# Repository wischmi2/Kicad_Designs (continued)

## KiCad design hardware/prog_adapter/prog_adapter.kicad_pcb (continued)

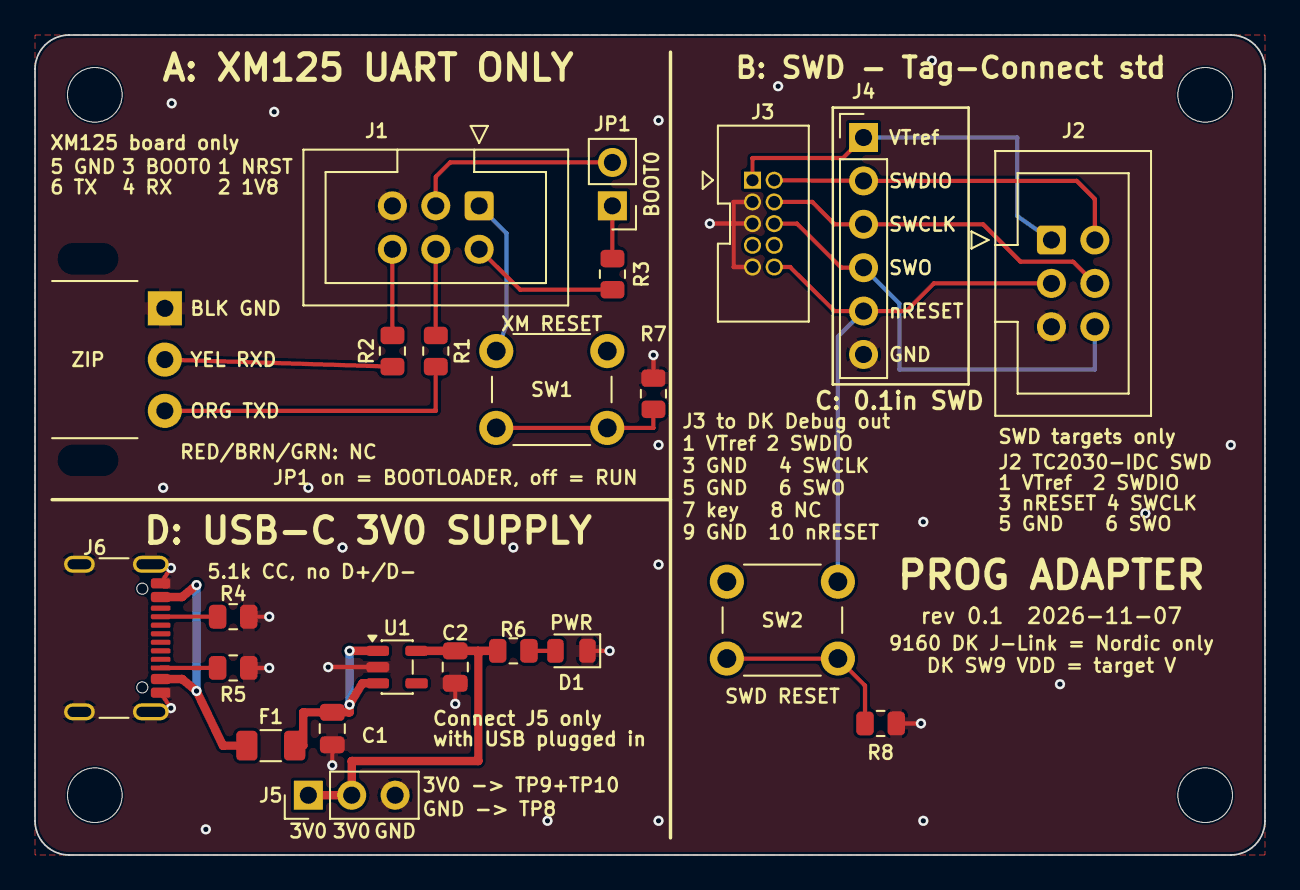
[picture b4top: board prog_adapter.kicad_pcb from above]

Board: 2 copper layers, 72.0 x 48.0 mm, 27 parts (0 on the bottom side), 22 nets.

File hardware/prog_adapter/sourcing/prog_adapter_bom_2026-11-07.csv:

Ref,Qty,Value,MPN,Manufacturer,DigiKey,Mouser,Unit price USD (qty 1),Stock 2026-11-07,Note
"J1,J2",2,2x3 box header,SSK05-BH-254-B3,Same Sky,2223-SSK05-BH-254-B3-ND,179-SSK05BH254B3,0.24,DK 1234 / Mouser 1977,shrouded keyed 2.54 mm THT
J3,1,2x5 1.27 mm box header,3220-10-0100-00,CNC Tech,1175-1627-ND,-,0.59,DK 648962,shrouded keyed THT; not found at Mouser
J4,1,1x6 2.54 mm header,PEC06SAAN,Sullins Connector Solutions,35-PEC06SAAN-ND,-,0.41,DK 24626,
J5,1,1x3 2.54 mm header,PEC03SAAN,Sullins Connector Solutions,35-PEC03SAAN-ND,-,0.22,DK 55156,
JP1,1,1x2 2.54 mm header,PEC02SAAN,Sullins Connector Solutions,35-PEC02SAAN-ND,-,0.16,DK 112334,
JP1 shunt,1,shunt 2.54 mm,SPC02SYAN,Sullins Connector Solutions,S9001-ND,-,0.10,DK 1441283,no footprint
J6,1,USB-C receptacle,USB4105-GF-A,GCT,2073-USB4105-GF-ACT-ND,640-USB4105-GF-A,0.80,DK 138469 / Mouser 390294,power only
"R1,R2",2,330R 0805,RC0805FR-07330RL,YAGEO,311-330CRCT-ND,603-RC0805FR-07330RL,0.10,DK 328688 / Mouser 337103,
"R3,R6",2,1k 0805,RC0805FR-071KL,YAGEO,311-1.00KCRCT-ND,603-RC0805FR-071KL,0.10,DK 407380 / Mouser 2104909,
"R4,R5",2,5.1k 0805,RC0805FR-075K1L,YAGEO,311-5.10KCRCT-ND,603-RC0805FR-075K1L,0.10,DK 1090000 / Mouser 126577,
"R7,R8",2,100R 0805,RC0805FR-07100RL,YAGEO,311-100CRCT-ND,603-RC0805FR-07100RL,0.10,DK 4667 / Mouser 221408,series with SW1/SW2 (review S1); live check 2026-11-07
"C1,C2",2,10u 25V X5R 0805,CC0805KKX5R8BB106,YAGEO,311-1869-1-ND,603-CC805KKX5R8BB106,0.44,DK 0 / Mouser 40574,buy at Mouser
D1,1,green LED 0805,LTST-C171GKT,Lite-On,160-1423-1-ND,859-LTST-C171GKT,0.15,DK 101891 / Mouser 207598,
F1,1,PTC 0.5 A 1206,MF-NSMF050-2,Bourns,MF-NSMF050-2CT-ND,652-MF-NSMF050-2,0.40,DK 60712 / Mouser 16856,
U1,1,LDO 3.0 V 500 mA SOT-23-5,TLV75530PDBVR,Texas Instruments,296-TLV75530PDBVRCT-ND,595-TLV75530PDBVR,0.32,DK 3168 / Mouser 16873,
"SW1,SW2",2,tact 6x6 THT,B3F-1000,Omron (Aratas),SW400-ND,653-B3F-1000,0.35,DK 20482 / Mouser 24727,
J7,0,FTDI wire pads,-,-,-,-,0,-,copper only (not a part)
"H1-H4",0,M3 holes,-,-,-,-,0,-,NPTH
CABLE,1,TC2030-IDC cable (legged),TC2030-IDC,Tag-Connect,TC2030-IDC-ND,-,44.58,DK 245,off-board; one cable serves J1 and J2
CABLE,1,1.8 V USB-UART,TTL-232RG-VREG1V8-WE,FTDI,768-1070-ND,895-TTL232RGVREG1V8W,27.34,DK 6 / Mouser 808,off-board; wires solder to J7
CABLE,1,10-pin 1.27 mm ribbon 6 in,FFSD-05-D-06.00-01-N,Samtec,SAM8218-ND,200-FFSD05D06.0001N,11.39,DK 1591 / Mouser 13408,off-board; DK Debug out to J3 (only if you don't have one)

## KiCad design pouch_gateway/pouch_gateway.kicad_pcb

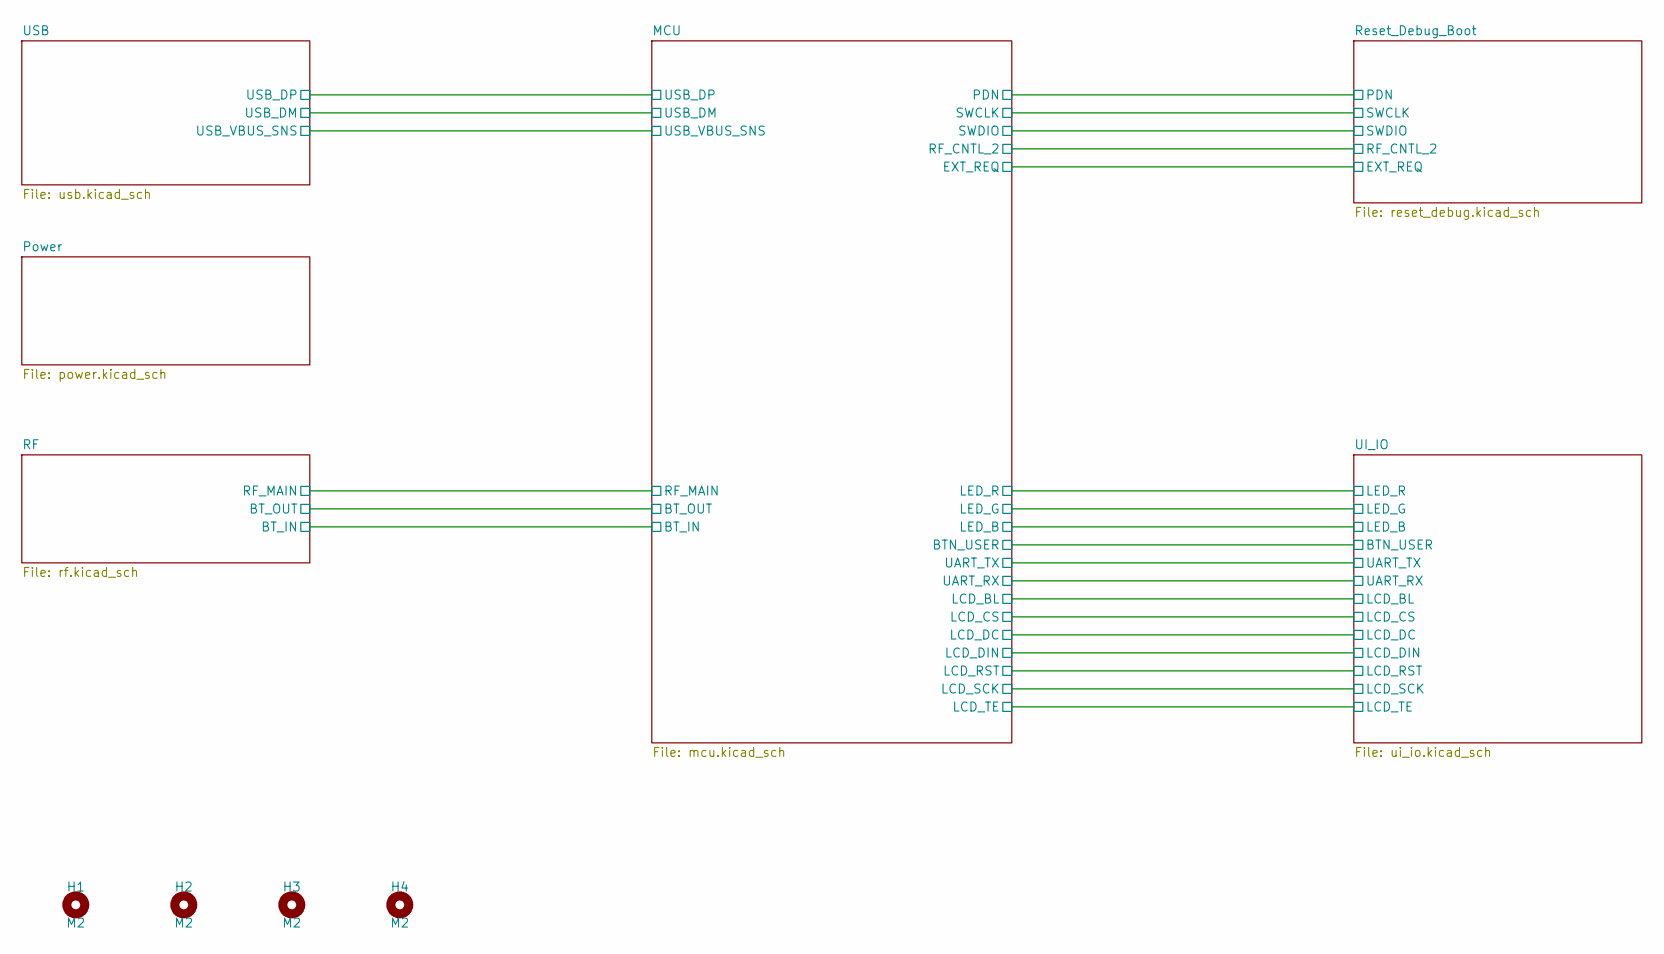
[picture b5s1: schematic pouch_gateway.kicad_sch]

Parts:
H1, H2, H3, H4: M2; MountingHole_2.2mm_M2

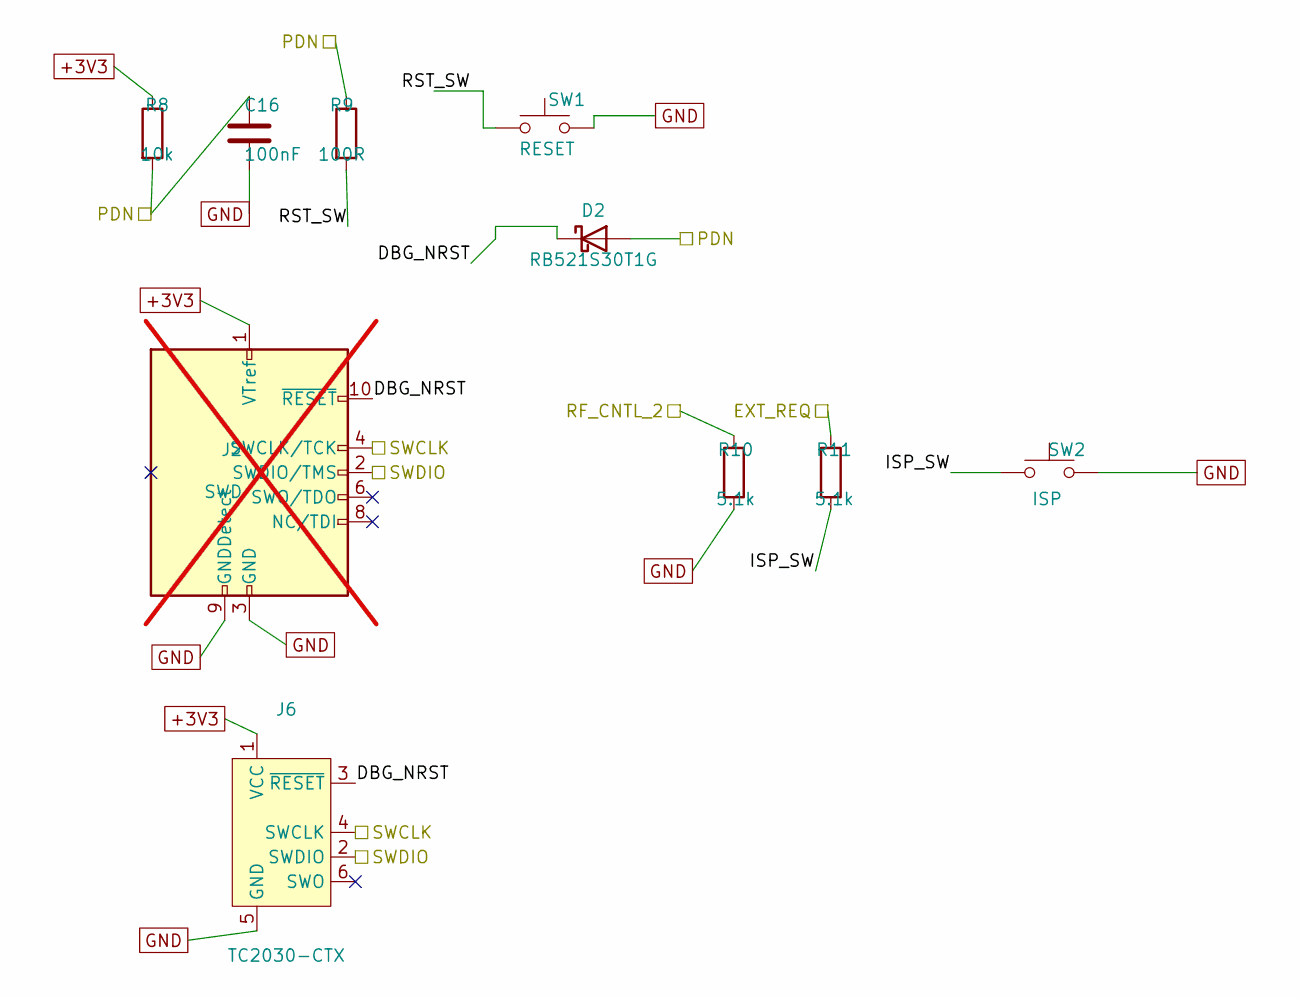
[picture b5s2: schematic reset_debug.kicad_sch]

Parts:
C16: 100nF; C_0402_1005Metric; LCSC C1525
D2: RB521S30T1G; D_SOD-523; LCSC C145179
J2: SWD; PinHeader_2x05_P1.27mm_Vertical_SMD; MPN FTSH-105-01-L-DV-K-TR; LCSC C448647; not fitted
J6: TC2030-CTX; Tag-Connect_TC2030-IDC-FP_2x03_P1.27mm_Vertical
R8: 10k; R_0402_1005Metric; LCSC C25744
R9: 100R; R_0402_1005Metric; LCSC C25076
R10, R11: 5.1k; R_0402_1005Metric; LCSC C25905
SW1: RESET; SW_Push_1P1T_NO_CK_KMR2; LCSC C72443
SW2: ISP; SW_Push_1P1T_NO_CK_KMR2; LCSC C72443

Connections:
+3V3: J2.1 (VTref), J6.1 (VCC), R8.1; also elsewhere on the board
/MCU/EXT_REQ: R11.1; also elsewhere on the board
/MCU/PDN: C16.1, D2.2 (A), R8.2, R9.1; also elsewhere on the board
/MCU/RF_CNTL_2: R10.1; also elsewhere on the board
/MCU/SWCLK: J2.4 (SWCLK/TCK), J6.4 (SWCLK); also elsewhere on the board
/MCU/SWDIO: J2.2 (SWDIO/TMS), J6.2 (SWDIO); also elsewhere on the board
/Reset_Debug_Boot/DBG_NRST: D2.1 (K), J2.10 (~RESET), J6.3 (~RESET)
/Reset_Debug_Boot/ISP_SW: R11.2, SW2.1
/Reset_Debug_Boot/RST_SW: R9.2, SW1.1
GND: C16.2, J2.3 (GND), J2.5 (GND), J2.9 (GNDDetect), J6.5 (GND), R10.2, SW1.2, SW2.2; also elsewhere on the board

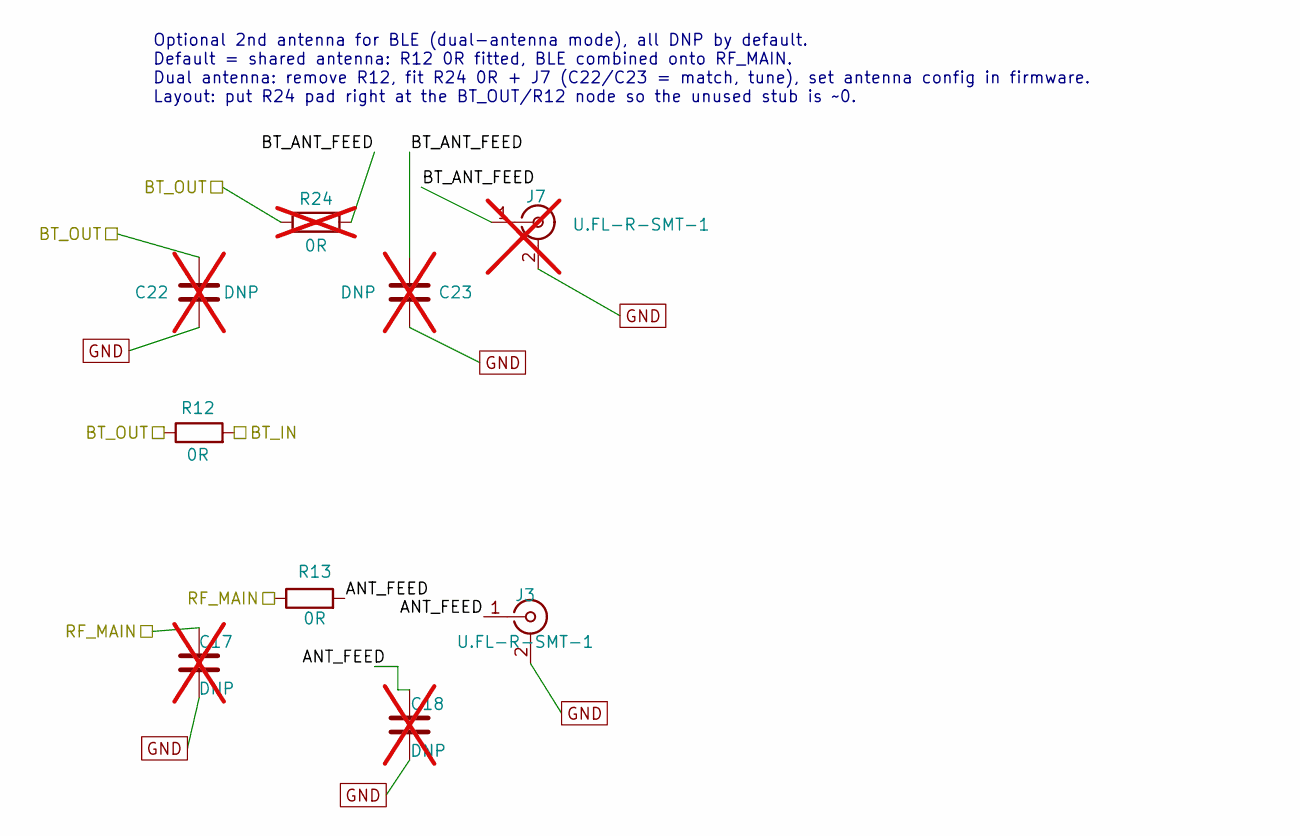
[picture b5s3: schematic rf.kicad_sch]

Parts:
C17, C18: DNP; C_0402_1005Metric; not fitted
C22, C23: DNP; C_0402_1005Metric; LCSC C1525; not fitted
J3: U.FL-R-SMT-1; U.FL_Hirose_U.FL-R-SMT-1_Vertical; LCSC C128668
J7: U.FL-R-SMT-1; U.FL_Hirose_U.FL-R-SMT-1_Vertical; LCSC C128668; not fitted
R12, R13: 0R; R_0402_1005Metric; LCSC C17168
R24: 0R; R_0402_1005Metric; LCSC C17168; not fitted

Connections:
/MCU/BT_IN: R12.2; also elsewhere on the board
/MCU/BT_OUT: C22.1, R12.1, R24.1; also elsewhere on the board
/MCU/RF_MAIN: C17.1, R13.1; also elsewhere on the board
/RF/ANT_FEED: C18.1, J3.1 (In), R13.2
/RF/BT_ANT_FEED: C23.1, J7.1 (In), R24.2
GND: C17.2, C18.2, C22.2, C23.2, J3.2 (Ext), J7.2 (Ext); also elsewhere on the board

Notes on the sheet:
Optional 2nd antenna for BLE (dual-antenna mode), all DNP by default. Default = shared antenna: R12 0R fitted, BLE combined onto RF_MAIN. Dual antenna: remove R12, fit R24 0R + J7 (C22/C23 = match, tune), set antenna config in firmware. Layout: put R24 pad right at the BT_OUT/R12 node so the unused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

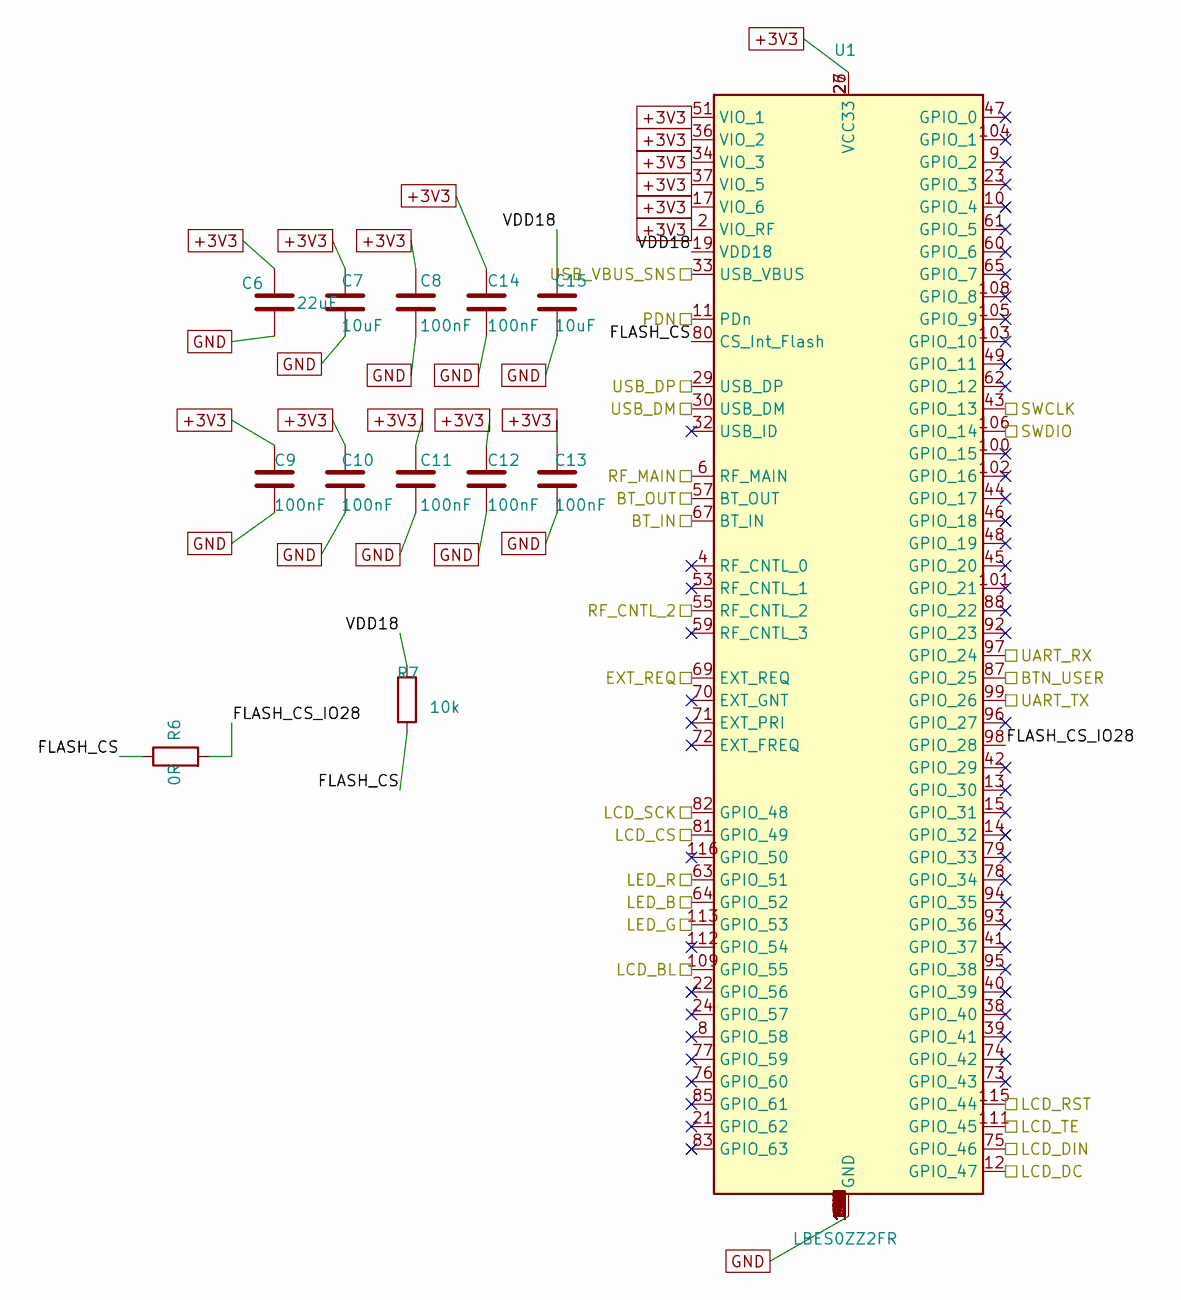
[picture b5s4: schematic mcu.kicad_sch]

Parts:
C6: 22uF; C_0805_2012Metric; LCSC C45783
C7, C15: 10uF; C_0603_1608Metric; LCSC C19702
C8, C9, C10, C11, C12, C13, C14: 100nF; C_0402_1005Metric; LCSC C1525
R6: 0R; R_0402_1005Metric; LCSC C17168
R7: 10k; R_0402_1005Metric; LCSC C25744
U1: LBES0ZZ2FR; Murata_LBES0ZZ2FR; MPN LBES0ZZ2FR-580

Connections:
+3V3: C6.1, C7.1, C8.1, C9.1, C10.1, C11.1, C12.1, C13.1, C14.1, U1.2 (VIO_RF), U1.17 (VIO_6), U1.26 (VCC33), U1.27 (VCC33), U1.34 (VIO_3), U1.36 (VIO_2), U1.37 (VIO_5), U1.51 (VIO_1); also elsewhere on the board
/MCU/BTN_USER: U1.87 (GPIO_25); also elsewhere on the board
/MCU/BT_IN: U1.67 (BT_IN); also elsewhere on the board
/MCU/BT_OUT: U1.57 (BT_OUT); also elsewhere on the board
/MCU/EXT_REQ: U1.69 (EXT_REQ); also elsewhere on the board
/MCU/FLASH_CS: R6.1, R7.2, U1.80 (CS_Int_Flash)
/MCU/FLASH_CS_IO28: R6.2, U1.98 (GPIO_28)
/MCU/LCD_BL: U1.109 (GPIO_55); also elsewhere on the board
/MCU/LCD_CS: U1.81 (GPIO_49); also elsewhere on the board
/MCU/LCD_DC: U1.12 (GPIO_47); also elsewhere on the board
/MCU/LCD_DIN: U1.75 (GPIO_46); also elsewhere on the board
/MCU/LCD_RST: U1.115 (GPIO_44); also elsewhere on the board
/MCU/LCD_SCK: U1.82 (GPIO_48); also elsewhere on the board
/MCU/LCD_TE: U1.111 (GPIO_45); also elsewhere on the board
/MCU/LED_B: U1.64 (GPIO_52); also elsewhere on the board
/MCU/LED_G: U1.113 (GPIO_53); also elsewhere on the board
/MCU/LED_R: U1.63 (GPIO_51); also elsewhere on the board
/MCU/PDN: U1.11 (PDn); also elsewhere on the board
/MCU/RF_CNTL_2: U1.55 (RF_CNTL_2); also elsewhere on the board
/MCU/RF_MAIN: U1.6 (RF_MAIN); also elsewhere on the board
/MCU/SWCLK: U1.43 (GPIO_13); also elsewhere on the board
/MCU/SWDIO: U1.106 (GPIO_14); also elsewhere on the board
/MCU/UART_RX: U1.97 (GPIO_24); also elsewhere on the board
/MCU/UART_TX: U1.99 (GPIO_26); also elsewhere on the board
/MCU/USB_DM: U1.30 (USB_DM); also elsewhere on the board
/MCU/USB_DP: U1.29 (USB_DP); also elsewhere on the board
/MCU/USB_VBUS_SNS: U1.33 (USB_VBUS); also elsewhere on the board
/MCU/VDD18: C15.1, R7.1, U1.19 (VDD18)
GND: C6.2, C7.2, C8.2, C9.2, C10.2, C11.2, C12.2, C13.2, C14.2, C15.2, U1.1 (GND), U1.3 (GND), U1.5 (GND), U1.7 (GND), U1.16 (GND), U1.18 (GND), U1.20 (GND), U1.25 (GND), U1.28 (GND), U1.31 (GND), U1.35 (GND), U1.50 (GND), U1.52 (GND), U1.54 (GND), U1.56 (GND), U1.58 (GND), U1.66 (GND), U1.68 (GND), U1.84 (GND), U1.86 (GND), U1.89 (GND), U1.90 (GND), U1.91 (GND), U1.107 (GND), U1.110 (GND), U1.114 (GND), U1.117 (GND), U1.118 (GND), U1.119 (GND), U1.120 (GND), U1.121 (GND), U1.122 (GND), U1.123 (GND), U1.124 (GND), U1.125 (GND), U1.126 (GND), U1.127 (GND), U1.128 (GND), U1.129 (GND), U1.130 (GND), U1.131 (GND), U1.132 (GND), U1.133 (GND), U1.134 (GND), U1.135 (GND), U1.136 (GND), U1.137 (GND), U1.138 (GND), U1.139 (GND), U1.140 (GND); also elsewhere on the board

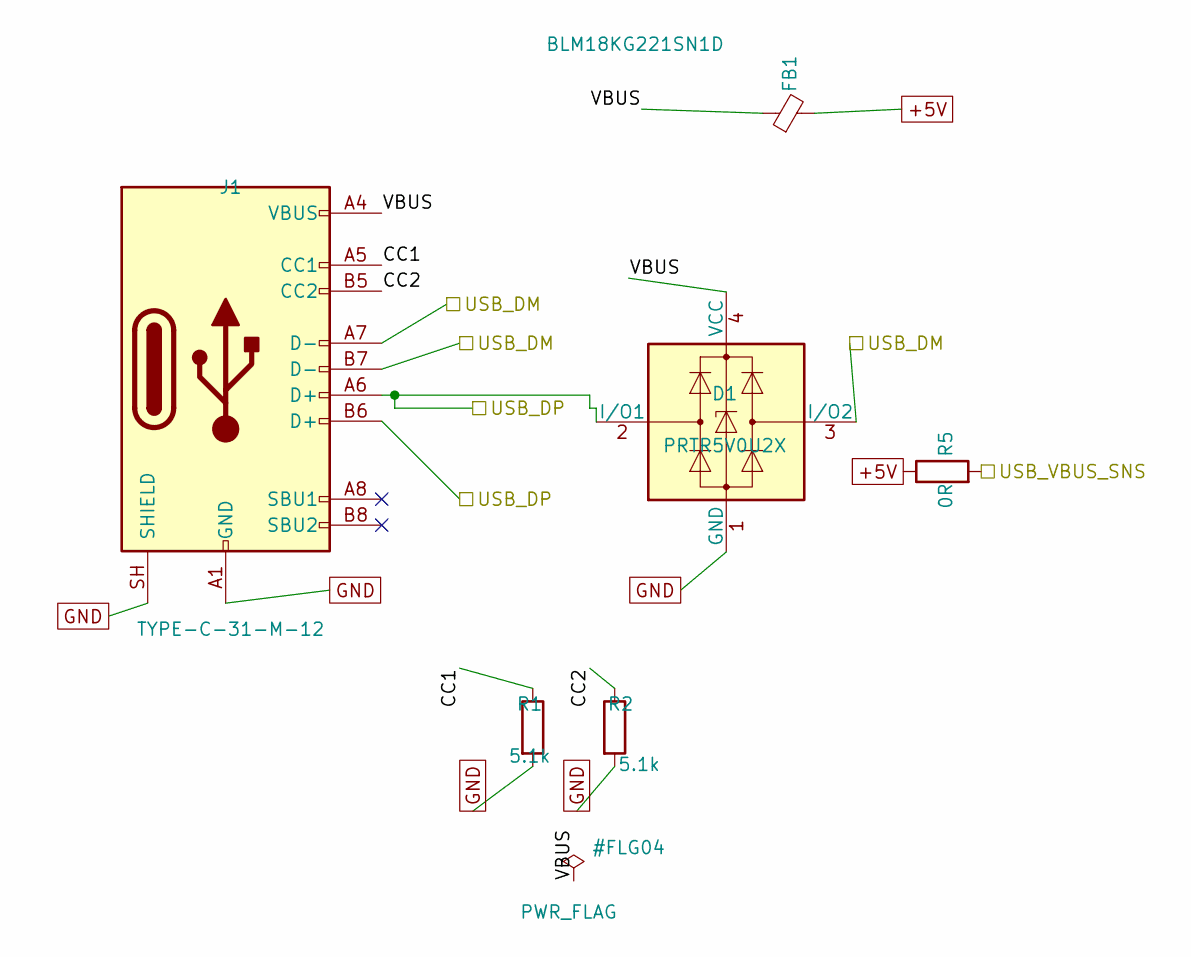
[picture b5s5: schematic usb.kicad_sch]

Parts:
D1: PRTR5V0U2X; SOT-143; LCSC C21713980
FB1: BLM18KG221SN1D; L_0603_1608Metric; LCSC C88980
J1: TYPE-C-31-M-12; USB_C_Receptacle_HRO_TYPE-C-31-M-12; LCSC C165948
R1, R2: 5.1k; R_0402_1005Metric; LCSC C25905
R5: 0R; R_0402_1005Metric; LCSC C17168

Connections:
+5V: FB1.2, R5.1; also elsewhere on the board
/MCU/USB_DM: D1.3 (I/O2), J1.A7 (D-), J1.B7 (D-); also elsewhere on the board
/MCU/USB_DP: D1.2 (I/O1), J1.A6 (D+), J1.B6 (D+); also elsewhere on the board
/MCU/USB_VBUS_SNS: R5.2; also elsewhere on the board
/USB/CC1: J1.A5 (CC1), R1.1
/USB/CC2: J1.B5 (CC2), R2.1
/USB/VBUS: D1.4 (VCC), FB1.1, J1.A4 (VBUS), J1.A9 (VBUS), J1.B4 (VBUS), J1.B9 (VBUS)
GND: D1.1 (GND), J1.A1 (GND), J1.A12 (GND), J1.B1 (GND), J1.B12 (GND), J1.SH (SHIELD), R1.2, R2.2; also elsewhere on the board

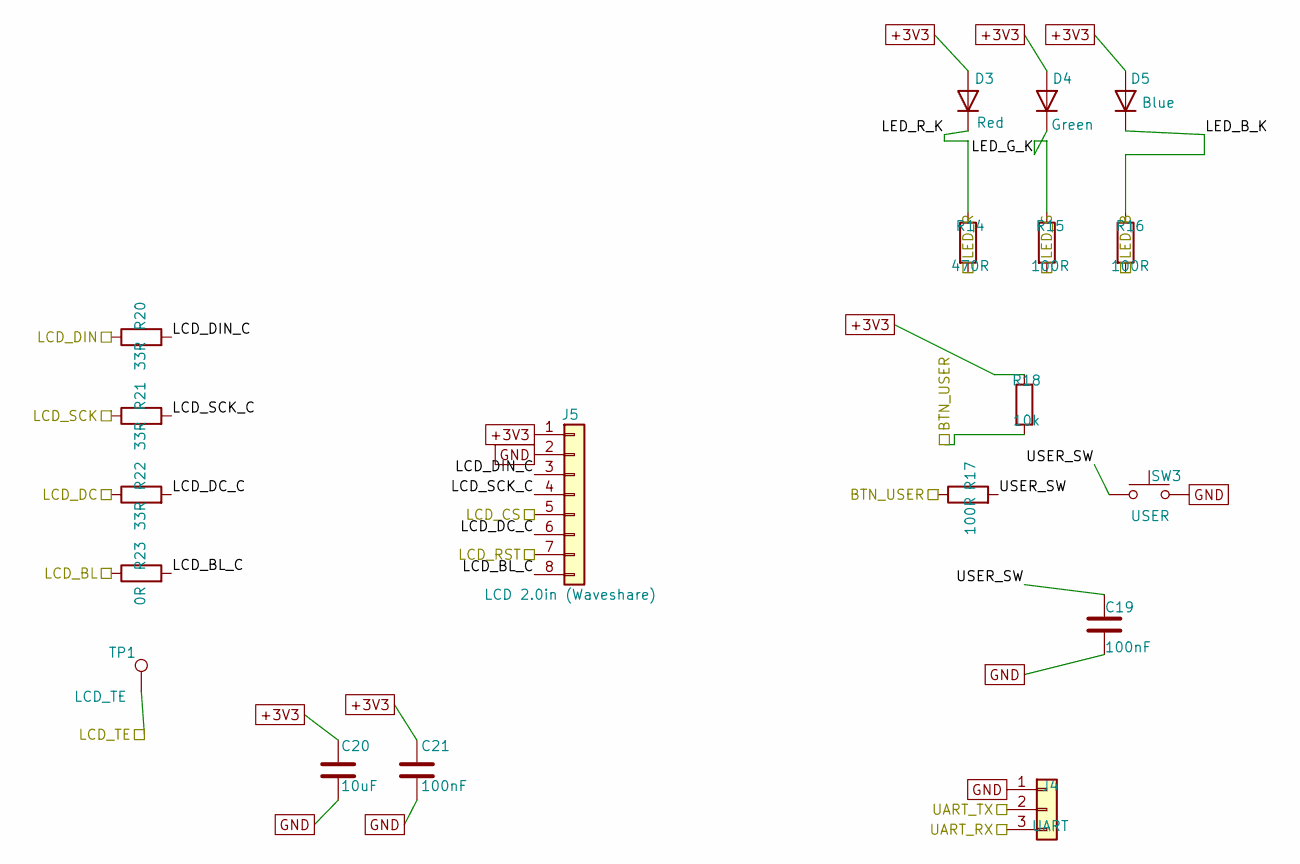
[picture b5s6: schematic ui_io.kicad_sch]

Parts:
C19, C21: 100nF; C_0402_1005Metric; LCSC C1525
C20: 10uF; C_0603_1608Metric; LCSC C19702
D3: Red; LED_0603_1608Metric; LCSC C2286
D4: Green; LED_0805_2012Metric; LCSC C2297
D5: Blue; LED_0603_1608Metric; LCSC C125096
J4: UART; PinHeader_1x03_P2.54mm_Vertical; MPN PZ254V-11-03P; LCSC C2937625
J5: LCD 2.0in (Waveshare); JST_PH_S8B-PH-K_1x08_P2.00mm_Horizontal; MPN S8B-PH-K-S(LF)(SN); LCSC C157915
R14: 470R; R_0402_1005Metric; LCSC C25117
R15, R16, R17: 100R; R_0402_1005Metric; LCSC C25076
R18: 10k; R_0402_1005Metric; LCSC C25744
R20, R21, R22: 33R; R_0402_1005Metric; LCSC C25105
R23: 0R; R_0402_1005Metric; LCSC C17168
SW3: USER; SW_Push_1P1T_NO_CK_KMR2; LCSC C72443
TP1: LCD_TE; TestPoint_Pad_D1.0mm

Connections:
+3V3: C20.1, C21.1, D3.2 (A), D4.2 (A), D5.2 (A), J5.1, R18.1; also elsewhere on the board
/MCU/BTN_USER: R17.1, R18.2; also elsewhere on the board
/MCU/LCD_BL: R23.1; also elsewhere on the board
/MCU/LCD_CS: J5.5; also elsewhere on the board
/MCU/LCD_DC: R22.1; also elsewhere on the board
/MCU/LCD_DIN: R20.1; also elsewhere on the board
/MCU/LCD_RST: J5.7; also elsewhere on the board
/MCU/LCD_SCK: R21.1; also elsewhere on the board
/MCU/LCD_TE: TP1.1 (1_1); also elsewhere on the board
/MCU/LED_B: R16.2; also elsewhere on the board
/MCU/LED_G: R15.2; also elsewhere on the board
/MCU/LED_R: R14.2; also elsewhere on the board
/MCU/UART_RX: J4.3; also elsewhere on the board
/MCU/UART_TX: J4.2; also elsewhere on the board
/UI_IO/LCD_BL_C: J5.8, R23.2
/UI_IO/LCD_DC_C: J5.6, R22.2
/UI_IO/LCD_DIN_C: J5.3, R20.2
/UI_IO/LCD_SCK_C: J5.4, R21.2
/UI_IO/LED_B_K: D5.1 (K), R16.1
/UI_IO/LED_G_K: D4.1 (K), R15.1
/UI_IO/LED_R_K: D3.1 (K), R14.1
/UI_IO/USER_SW: C19.1, R17.2, SW3.1
GND: C19.2, C20.2, C21.2, J4.1, J5.2, SW3.2; also elsewhere on the board

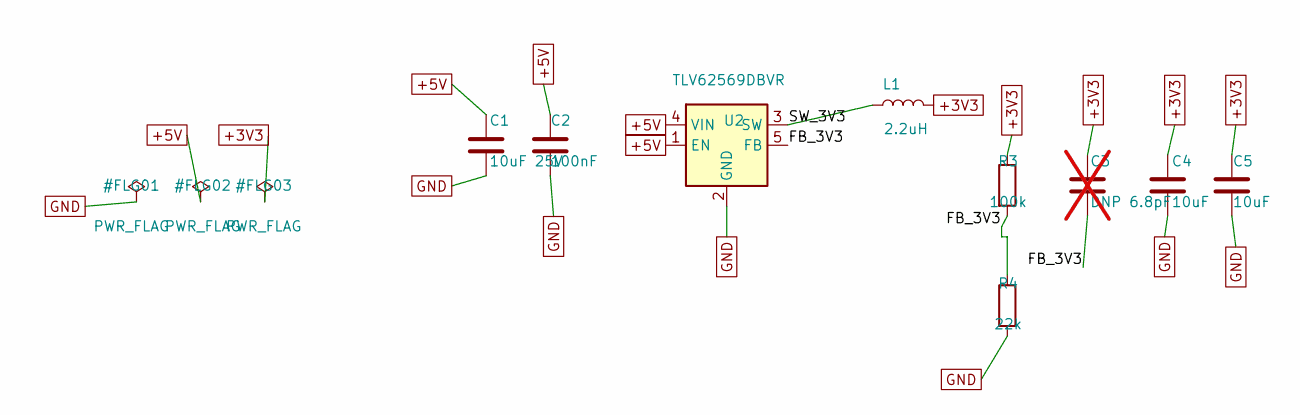
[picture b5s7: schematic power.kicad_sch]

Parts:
C1: 10uF 25V; C_0603_1608Metric; LCSC C96446
C2: 100nF; C_0402_1005Metric; LCSC C1525
C3: DNP 6.8pF; C_0402_1005Metric; not fitted
C4, C5: 10uF; C_0603_1608Metric; LCSC C19702
L1: 2.2uH; L_Sunlord_SWPA4020S; MPN SWPA4020S2R2MT; LCSC C83423
R3: 100k; R_0402_1005Metric; LCSC C25741
R4: 22k; R_0402_1005Metric; LCSC C25768
U2: TLV62569DBVR; SOT-23-5; LCSC C141836

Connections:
+3V3: C3.1, C4.1, C5.1, L1.2, R3.1; also elsewhere on the board
+5V: C1.1, C2.1, U2.1 (EN), U2.4 (VIN); also elsewhere on the board
/Power/FB_3V3: C3.2, R3.2, R4.1, U2.5 (FB)
/Power/SW_3V3: L1.1, U2.3 (SW)
GND: C1.2, C2.2, C4.2, C5.2, R4.2, U2.2 (GND); also elsewhere on the board

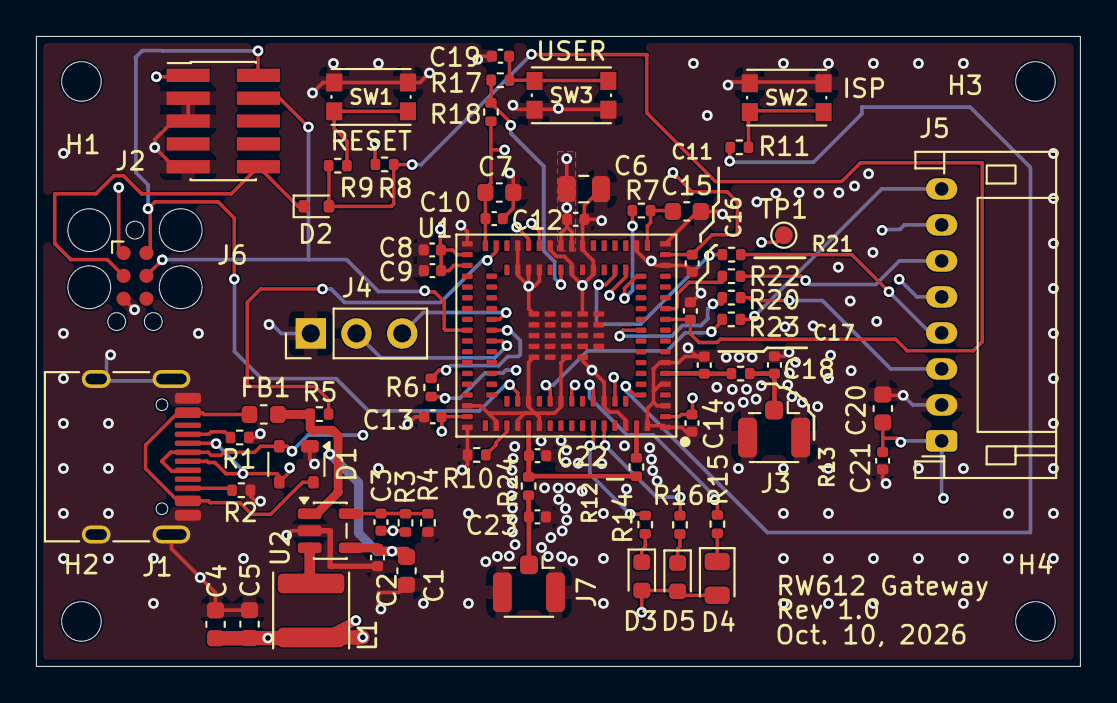
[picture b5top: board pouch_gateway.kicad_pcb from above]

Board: 4 copper layers, 58.0 x 35.0 mm, 70 parts (0 on the bottom side), 48 nets.

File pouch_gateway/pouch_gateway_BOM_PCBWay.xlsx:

|  |  | pouch_gateway — PCB Assembly BOM
Item # | *Designator | *Qty | Manufacturer | *Mfg Part # | Description / Value | *Package/Footprint | Type | Your Instructions / Notes
1 | C2,C8,C9,C10,C11,C12,C13,C14,C16,C19,C21 | 11 | Samsung Electro-Mechanics | CL05B104KO5NNNC | CAP CER 100nF 16V X7R ±10% 0402 | 0402 | SMD | LCSC: C1525
2 | C1 | 1 | Samsung Electro-Mechanics | CL10A106MA8NRNC | CAP CER 10uF 25V X5R ±20% 0603 | 0603 | SMD | LCSC: C96446 (25V rating required)
3 | C4,C5,C7,C15,C20 | 5 | Samsung Electro-Mechanics | CL10A106KP8NNNC | CAP CER 10uF 10V X5R ±10% 0603 | 0603 | SMD | LCSC: C19702
4 | C6 | 1 | Samsung Electro-Mechanics | CL21A226MAQNNNE | CAP CER 22uF 25V X5R ±20% 0805 | 0805 | SMD | LCSC: C45783
5 | R5,R6,R12,R13,R23 | 5 | UNI-ROYAL | 0402WGF0000TCE | RES 0 OHM JUMPER 1/16W 0402 | 0402 | SMD | LCSC: C17168
6 | R1,R2,R10,R11 | 4 | UNI-ROYAL | 0402WGF5101TCE | RES 5.1K OHM 1% 1/16W 0402 | 0402 | SMD | LCSC: C25905
7 | R7,R8,R18 | 3 | UNI-ROYAL | 0402WGF1002TCE | RES 10K OHM 1% 1/16W 0402 | 0402 | SMD | LCSC: C25744
8 | R3 | 1 | UNI-ROYAL | 0402WGF1003TCE | RES 100K OHM 1% 1/16W 0402 | 0402 | SMD | LCSC: C25741
9 | R4 | 1 | UNI-ROYAL | 0402WGF2202TCE | RES 22K OHM 1% 1/16W 0402 | 0402 | SMD | LCSC: C25768
10 | R9,R15,R16,R17 | 4 | UNI-ROYAL | 0402WGF1000TCE | RES 100 OHM 1% 1/16W 0402 | 0402 | SMD | LCSC: C25076
11 | R14 | 1 | UNI-ROYAL | 0402WGF4700TCE | RES 470 OHM 1% 1/16W 0402 | 0402 | SMD | LCSC: C25117
12 | R20,R21,R22 | 3 | UNI-ROYAL | 0402WGF330JTCE | RES 33 OHM 1% 1/16W 0402 | 0402 | SMD | LCSC: C25105
13 | FB1 | 1 | Murata | BLM18KG221SN1D | FERRITE BEAD 220 OHM @100MHz 2.2A 0603 | 0603 | SMD | LCSC: C88980
14 | L1 | 1 | Sunlord | SWPA4020S2R2MT | INDUCTOR PWR 2.2uH ±20% 4x4mm SMD | SMD 4.0x4.0mm | SMD | LCSC: C83423
15 | D1 | 1 | GOODWORK | PRTR5V0U2X | TVS ESD 2-CH USB PROTECTION SOT-143 | SOT-143 | SMD | LCSC: C21713980; Nexperia PRTR5V0U2X acceptable alternate. Polarity per silkscr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
16 | D2 | 1 | onsemi | RB521S30T1G | DIODE SCHOTTKY 30V 200mA SOD-523 | SOD-523 | SMD | LCSC: C145179; polarity per silkscreen
17 | D3 | 1 | Hubei KENTO | KT-0603R | LED RED 0603 | 0603 | SMD | LCSC: C2286; polarity per silkscreen
18 | D4 | 1 | Hubei KENTO | KT-0805G | LED GREEN 0805 | 0805 | SMD | LCSC: C2297; polarity per silkscreen
19 | D5 | 1 | Lite-On | LTST-C190TBKT | LED BLUE 0603 | 0603 | SMD | LCSC: C125096; polarity per silkscreen
20 | U1 | 1 | Murata | LBES0ZZ2FR-580 | MODULE WI-FI/BLE (Murata Type 2FR) | Murata LBES0ZZ2FR module, SMD | SMD | No LCSC part #; please quote sourcing. Pin 1 per silkscreen
21 | U2 | 1 | Texas Instruments | TLV62569DBVR | IC REG BUCK ADJ 2A SOT-23-5 | SOT-23-5 | SMD | LCSC: C141836; pin 1 per silkscreen
22 | J1 | 1 | Korean Hroparts Elec (HRO) | TYPE-C-31-M-12 | CONN USB TYPE-C RCPT 16P SMD R/A | SMD | SMD | LCSC: C165948
23 | J2 | 1 | Samtec | FTSH-105-01-L-DV-K-TR | CONN HDR 2x5 1.27mm SMD VERT (SWD) | 2x5 P1.27mm SMD | SMD | LCSC: C448647; pin 1 per silkscreen
24 | J3 | 1 | Hirose | U.FL-R-SMT-1(60) | CONN U.FL RF COAX RCPT SMD | SMD | SMD | LCSC: C128668
25 | ISP,RESET,USER | 3 | C&K | KMR221GLFS | SWITCH TACTILE SPST-NO 50mA 32V SMD | SMD 4.6x2.8mm | SMD | LCSC: C72443
26 | J4 | 1 | XFCN | PZ254V-11-03P | CONN HDR 1x3 2.54mm VERT THT | 1x3 P2.54mm THT | thru-hole | LCSC: C2937625
27 | J5 | 1 | JST | S8B-PH-K-S(LF)(SN) | CONN HDR PH 8POS 2.0mm R/A THT | 1x8 P2.00mm R/A THT | thru-hole | LCSC: C157915
28 | C3 | 1 |  |  | CAP CER 6.8pF 0402 (not fitted) | 0402 | DNS | Do not populate
29 | C17,C18 | 2 |  |  | CAP CER 0402 (not fitted) | 0402 | DNS | Do not populate
30 | C22,C23 | 2 |  |  | CAP CER 100nF 0402 (not fitted) | 0402 | DNS | Do not populate
31 | R24 | 1 |  |  | RES 0 OHM 0402 (not fitted) | 0402 | DNS | Do not populate
32 | J7 | 1 |  |  | CONN U.FL RF COAX RCPT SMD (not fitted) | SMD | DNS | Do not populate
Need a quick and accurante quote? Need an efficient production? Please read SMT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
Click for Instructions on How to Create a BOM

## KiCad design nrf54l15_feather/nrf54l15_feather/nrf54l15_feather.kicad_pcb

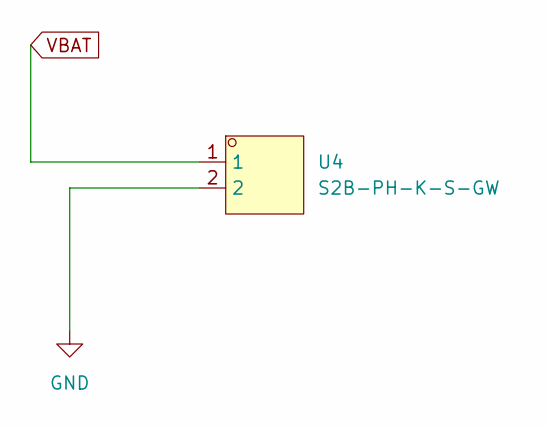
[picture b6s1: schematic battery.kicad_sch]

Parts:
U4: S2B-PH-K-S-GW; CONN-TH_S2B-PH-K-S-GW; MPN S2B-PH-K-S-GW; LCSC Part C157932

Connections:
GND: U4.2; also elsewhere on the board
VBAT: U4.1; also elsewhere on the board

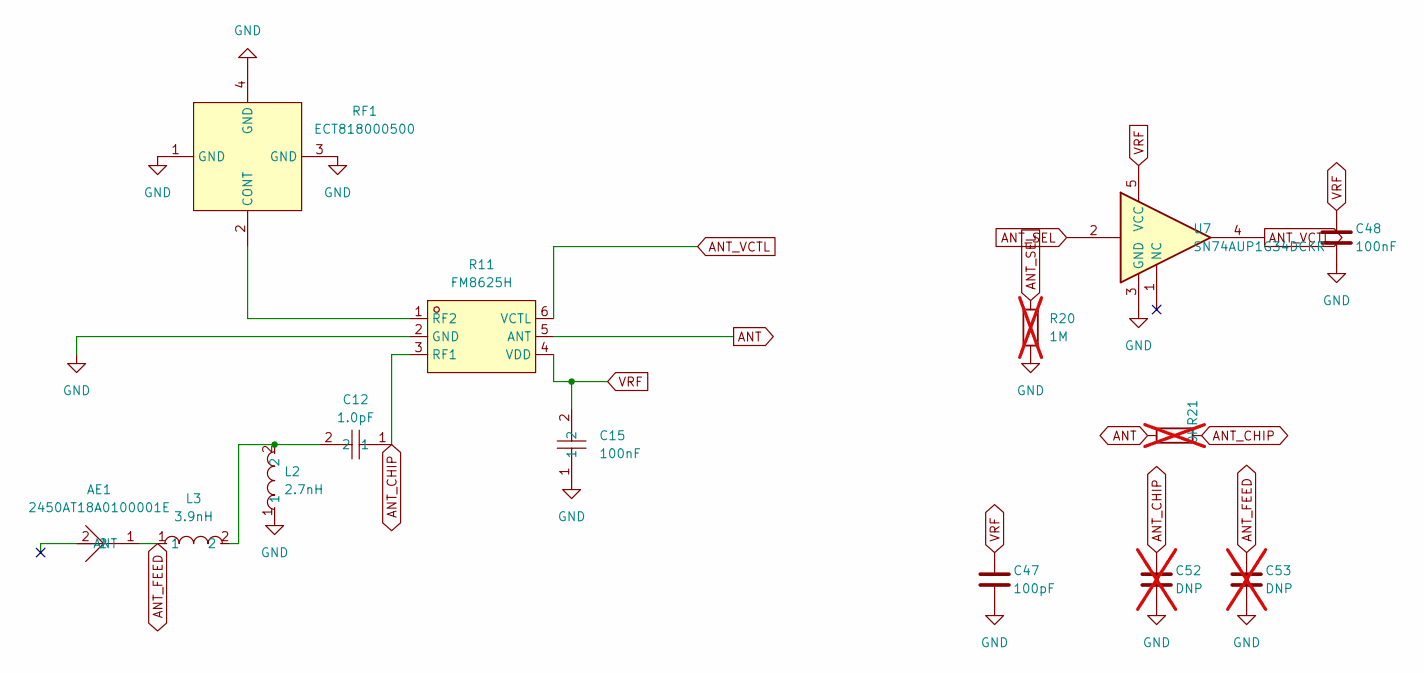
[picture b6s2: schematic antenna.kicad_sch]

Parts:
AE1: 2450AT18A0100001E; ANT-SMD_L3.2-W1.6; Mouser PN 609-2450AT18A0100001
C12: 1.0pF; C0201; MPN GJM0335C1E1R0WB01D; LCSC Part C185624
C15: 100nF; C0603; MPN CC0603KRX7R9BB104; LCSC Part C14663
C47: 100pF; C_0402_1005Metric; MPN CL05C101JB5NNNC; LCSC C26409
C48: 100nF; C_0402_1005Metric; Mouser PN 81-GCM155R71C104KA5D
C52, C53: DNP; C_0201_0603Metric; not fitted
L2: 2.7nH; L0201; MPN LQP03HQ2N7B02D; LCSC Part C7216765
L3: 3.9nH; L0201; MPN LQP03HQ3N9B02D; LCSC Part C337939
R11: FM8625H; DFN-6_L1.1-W0.7-P0.40-BL; MPN FM8625H; LCSC Part C2857391
R20: 1M; R_0402_1005Metric; MPN 0402WGF1004TCE; LCSC C26083; not fitted
R21: 0R; R_0402_1005Metric; MPN 0402WGF0000TCE; LCSC C17168; not fitted
RF1: ECT818000500; ANT-SMD_ECT818000500; MPN ECT818000500; LCSC Part C437254
U7: SN74AUP1G34DCKR; SOT-353_SC-70-5; MPN SN74AUP1G34DCKR; LCSC C2675656

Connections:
ANT: R11.5 (ANT), R21.1; also elsewhere on the board
ANT_CHIP: C12.1, C52.1, R11.3 (RF1), R21.2
ANT_FEED: AE1.1 (ANT_1), C53.1, L3.1
ANT_SEL: R20.1, U7.2; also elsewhere on the board
ANT_VCTL: R11.6 (VCTL), U7.4
GND: C15.1, C47.2, C48.2, C52.2, C53.2, L2.1, R11.2 (GND), R20.2, RF1.1 (GND), RF1.3 (GND), RF1.4 (GND), U7.3 (GND); also elsewhere on the board
unnamed: C12.2, L2.2, L3.2
unnamed: R11.1 (RF2), RF1.2 (CONT)
VRF: C15.2, C47.1, C48.1, R11.4 (VDD), U7.5 (VCC); also elsewhere on the board
